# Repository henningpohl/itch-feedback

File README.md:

# Itch Feedback
This is a repository for content related to the [*ElectricItch: Skin Irritation as a Feedback Modality*](https://doi.org/10.1145/3242587.3242647) paper, published at [UIST 2018](https://uist.acm.org/uist2018/).

## Contents
At this point, this repository contains:
 - The paper itself
 - The schematics and board layout for [Autodesk EAGLE](https://www.autodesk.com/products/eagle/overview)
 - Firmware code for the [Adafruit Feather M0 Bluefruit LE](https://www.adafruit.com/product/2995), as a [Platform.IO](http://platformio.org/platformio-ide) project (likely works with other boards and IDEs)

## License
See the LICENSE file. Basically all our work is released under the MIT License --- do whatever you want with it. Note though that the firmware uses the [Timer5 library](https://github.com/michael71/Timer5), which is licensed under the GNU LGPL.

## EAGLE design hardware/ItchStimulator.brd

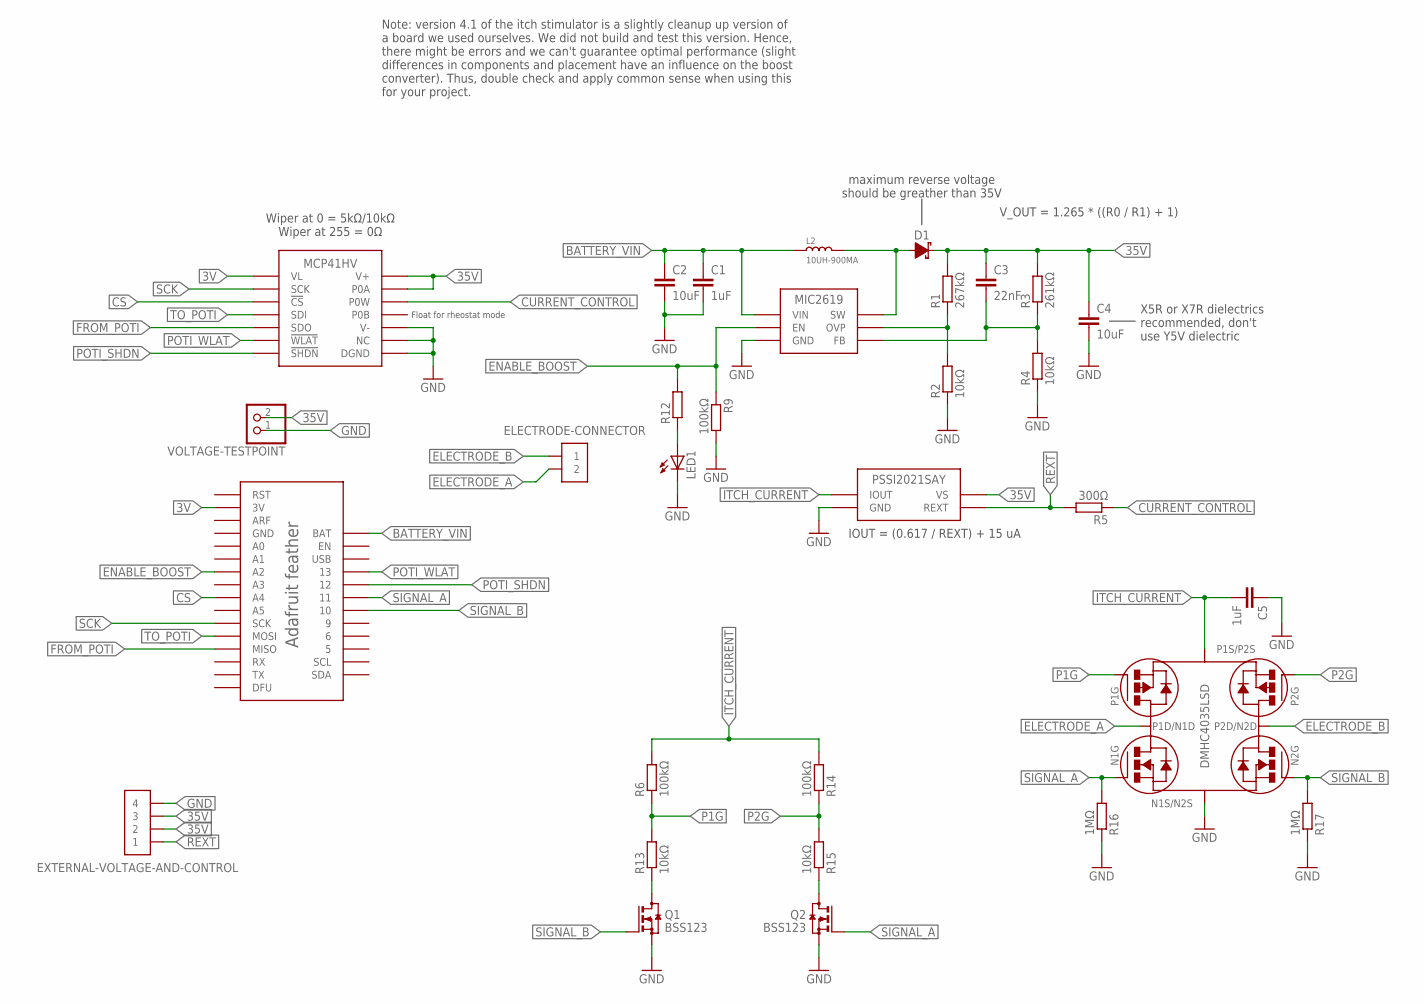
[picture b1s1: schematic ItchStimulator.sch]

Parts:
C1, C5: 1uF; C0805K
C2, C4: 10uF; C0805K
C3: 22nF; C0805K
D1: DIODE-SCHOTTKY; DO-214AA
ELECTRODE-CONNECTOR: 2-PIN_HEADER; SAMTEC-TSM-102-01-X-SH
EXTERNAL-VOLTAGE-AND-CONTROL: 4-PIN_HEADER; SAMTEC-TSM-104-01-X-SH
L2: 10UH-900MA; L1210
LED1: LEDSML0805; SML0805
MCP41HV: MCP41HV; TSSOP-14
MIC2619: MIC2619; TSOT-23-6
PSSI2021SAY: PSSI2021SAY; SOT-353
Q1, Q2: BSS123; SOT23
R1: 267kΩ; R0805
R2, R4, R13, R15: 10kΩ; R0805
R3: 261kΩ; R0805
R5: 300Ω; R0805
R6, R9, R14: 100kΩ; R0805
R12: R-EU_R0805; R0805
R16, R17: 1MΩ; R0805
U$1: ADAFRUIT_FEATHER_M0_BLUETOOTH
U$2: DMHC4035LSD; SOIC-8
VOLTAGE-TESTPOINT: PINHD-1X2; 1X02

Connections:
3V: MCP41HV.P$1 (VL), U$1.P$15 (3V)
35V: C3.1, C4.1, D1.CATHODE, EXTERNAL-VOLTAGE-AND-CONTROL.P$2 (2), EXTERNAL-VOLTAGE-AND-CONTROL.P$3 (3), MCP41HV.P$13 (P0A), MCP41HV.P$14 (V+), PSSI2021SAY.P$5 (VS), R1.2, R3.2, VOLTAGE-TESTPOINT.2
BATTERY_VIN: C1.1, C2.1, L2.1, MIC2619.P$6 (VIN), U$1.P$17 (BAT)
CS: MCP41HV.P$3 (!CS), U$1.P$8 (A4)
CURRENT_CONTROL: MCP41HV.P$12 (P0W), R5.1
ELECTRODE_A: ELECTRODE-CONNECTOR.P$2 (2), U$2.P$2 (P1D/N1D)
ELECTRODE_B: ELECTRODE-CONNECTOR.P$1 (1), U$2.P$6 (P2D/N2D)
ENABLE_BOOST: MIC2619.P$4 (EN), R9.1, R12.2, U$1.P$10 (A2)
FROM_POTI: MCP41HV.P$5 (SDO), U$1.P$4 (MISO)
GND: C1.2, C2.2, C4.2, C5.1, EXTERNAL-VOLTAGE-AND-CONTROL.P$4 (4), LED1.C, MCP41HV.P$8 (DGND), MCP41HV.P$9 (NC), MCP41HV.P$10 (V-), MIC2619.P$2 (GND), PSSI2021SAY.P$3 (GND), Q1.2 (S), Q2.2 (S), R2.1, R4.1, R9.2, R16.1, R17.1, U$1.P$13 (GND), U$2.P$3 (N1S/N2S), VOLTAGE-TESTPOINT.1
ITCH_CURRENT: C5.2, PSSI2021SAY.P$2 (IOUT), R6.2, R14.2, U$2.P$7 (P1S/P2S)
unnamed: D1.ANODE, L2.2, MIC2619.P$1 (SW)
unnamed: C3.2, MIC2619.P$3 (FB), R3.1, R4.2
unnamed: LED1.A, R12.1
unnamed: MIC2619.P$5 (OVP), R1.1, R2.2
unnamed: Q1.3 (D), R13.1
unnamed: Q2.3 (D), R15.1
P1G: R6.1, R13.2, U$2.P$8 (P1G)
P2G: R14.1, R15.2, U$2.P$5 (P2G)
POTI_SHDN: MCP41HV.P$7 (!SHDN), U$1.P$21 (12)
POTI_WLAT: MCP41HV.P$6 (!WLAT), U$1.P$20 (13)
REXT: EXTERNAL-VOLTAGE-AND-CONTROL.P$1 (1), PSSI2021SAY.P$4 (REXT), R5.2
SCK: MCP41HV.P$2 (SCK), U$1.P$6 (SCK)
SIGNAL_A: Q2.1 (G), R16.2, U$1.P$22 (11), U$2.P$1 (N1G)
SIGNAL_B: Q1.1 (G), R17.2, U$1.P$23 (10), U$2.P$4 (N2G)
TO_POTI: MCP41HV.P$4 (SDI), U$1.P$5 (MOSI)
USB: U$1.P$19 (USB)

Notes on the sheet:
X5R or X7R dielectrics recommended, don't use Y5V dielectric
maximum reverse voltage should be greather than 35V
V_OUT = 1.265 * ((R0 / R1) + 1)
IOUT = (0.617 / REXT) + 15 uA
Float for rheostat mode
Wiper at 0 = 5kΩ/10kΩ Wiper at 255 = 0Ω
Note: version 4.1 of the itch stimulator is a slightly cleanup up version of a board we used ourselves. We did not build and test this version. Hence, there might be errors and we can't guarantee optimal performance (slight differences in components and placement have an influence on the boost conv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

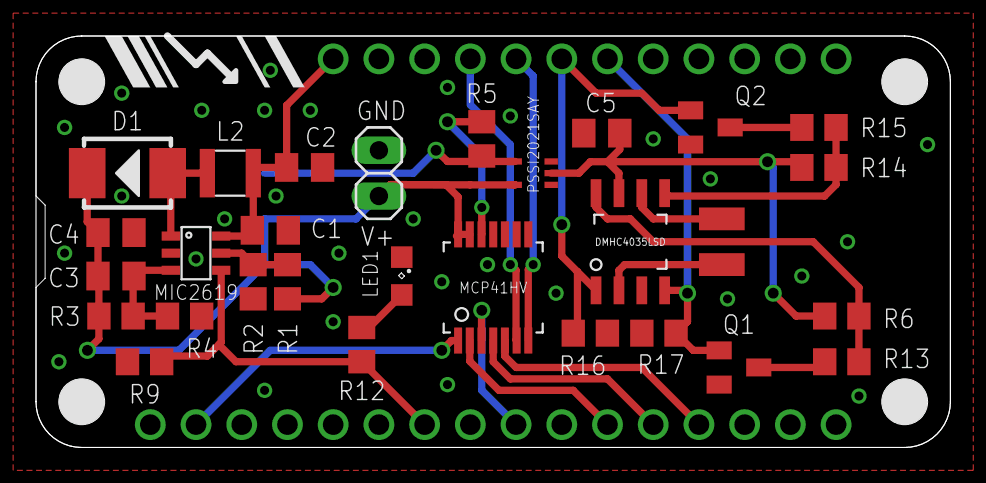
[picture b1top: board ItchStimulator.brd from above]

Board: 2 copper layers, 50.8 x 22.9 mm, 31 parts (1 on the bottom side), 26 nets.

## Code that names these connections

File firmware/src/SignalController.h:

#pragma once

#include "Timer5.h"
#include "MCP41HV.h"
#include "CommandParser.h"

const int SIGNAL_A = 11;
const int SIGNAL_B = 10;
const int BOOST_ENABLE = A2;

const int POTI_CS = A4;
const int POTI_WLAT = 13;
const int POTI_SHDN = 12;
MCP41HV poti(POTI_CS);

bool isTurnedOn = false;

#if INCLUDE_TESTS
  typedef void (* LoopFunction)();
  LoopFunction loopTestFunction = nullptr;
#endif


const uint16_t TIMER_TICKS = 32768;
const double MICROSECONDS_TO_TICKS = TIMER_TICKS / 1000000.0;
uint16_t signalToggle = 655; // 50Hz
uint16_t pulseToggle = 65; // 2ms pulse
uint16_t curTimerState = 0;

void Timer5_IRQ() {
  if(!isTurnedOn) {
    return;
  }

  if(curTimerState == 0) {
    digitalWrite(SIGNAL_A, HIGH);
  } else if(curTimerState == pulseToggle) {
    digitalWrite(SIGNAL_A, LOW);
  } else if(curTimerState == pulseToggle + 20) {
    digitalWrite(SIGNAL_B, HIGH);
  } else if(curTimerState == (2 * pulseToggle + 20)) {
    digitalWrite(SIGNAL_B, LOW);
  }
  
  curTimerState = (curTimerState + 1) % (signalToggle + 1);
}

void onParameterChange(SignalParameters & params) {
  poti.writeWiperValue(params.amplitude);
  signalToggle = TIMER_TICKS / params.frequency;
  pulseToggle = params.pulseWidth * MICROSECONDS_TO_TICKS; 
  curTimerState = 0;
}

void setupSignal() {
  pinMode(POTI_WLAT, OUTPUT);
  pinMode(POTI_SHDN, OUTPUT);
  pinMode(SIGNAL_A, OUTPUT);
  pinMode(SIGNAL_B, OUTPUT);
  pinMode(BOOST_ENABLE, OUTPUT);

  poti.setup();
  SPI.begin();

  MyTimer5.begin(1); // run at full 32768 Hz
  MyTimer5.attachInterrupt(Timer5_IRQ);

  digitalWrite(BOOST_ENABLE, LOW);
  digitalWrite(POTI_WLAT, LOW); // Don't delay wiper value updates
  digitalWrite(POTI_SHDN, LOW); // Shut down initially
  digitalWrite(SIGNAL_A, LOW);
  digitalWrite(SIGNAL_B, LOW);
}

void turnOnSignal() {
#if INCLUDE_TESTS
  loopTestFunction = nullptr;
#endif

  isTurnedOn = true;
  digitalWrite(BOOST_ENABLE, HIGH);
  digitalWrite(POTI_SHDN, HIGH);
  MyTimer5.begin(1); // run at full 32768 Hz
  MyTimer5.start();
}

void turnOffSignal() {
#if INCLUDE_TESTS
  loopTestFunction = nullptr;
#endif

  isTurnedOn = false;
  digitalWrite(BOOST_ENABLE, LOW);
  digitalWrite(POTI_SHDN, LOW);
  MyTimer5.end();
}

#if INCLUDE_TESTS
void constantTestSignal(uint8_t strength) {
  isTurnedOn = false;
  MyTimer5.end();
  digitalWrite(BOOST_ENABLE, HIGH);
  digitalWrite(POTI_SHDN, HIGH);
  poti.writeWiperValue(strength);
  digitalWrite(SIGNAL_A, LOW);
  digitalWrite(SIGNAL_B, HIGH);

}

uint8_t rampTestState;
void rampLoopFunction() {
  poti.writeWiperValue(rampTestState);
  rampTestState--;
  digitalWrite(SIGNAL_A, LOW);
  digitalWrite(SIGNAL_B, HIGH);
  delayMicroseconds(2000);
  digitalWrite(SIGNAL_A, LOW);
  digitalWrite(SIGNAL_B, LOW);
}

void rampTestSignal() {
  isTurnedOn = false;
  MyTimer5.end();
  digitalWrite(BOOST_ENABLE, HIGH);
  digitalWrite(POTI_SHDN, HIGH);
  digitalWrite(SIGNAL_A, LOW);
  digitalWrite(SIGNAL_B, LOW);
  rampTestState = 255;
  poti.writeWiperValue(rampTestState);
  loopTestFunction = rampLoopFunction;
}

void testSignalOutput() {
  digitalWrite(POTI_SHDN, HIGH);
  poti.writeWiperValue(234); // should be 1.5mA -> 15V over the 10k resistor
  isTurnedOn = true;
  MyTimer5.begin(1); // run at full 32768 Hz
  MyTimer5.start();
}

void testSignalOutput2() {
  digitalWrite(POTI_SHDN, HIGH);
  poti.writeWiperValue(220);
  digitalWrite(SIGNAL_B, HIGH);
  delay(2000);
  digitalWrite(SIGNAL_B, LOW);
  delay(2000);
  digitalWrite(SIGNAL_A, HIGH);
  delay(2000);
  digitalWrite(SIGNAL_A, LOW);
  delay(2000);
}

void selectTestMode(uint32_t testMode) {
  switch(testMode) {
    case 0:
      constantTestSignal(255);
      break;
    case 1:
      constantTestSignal(200);
      break;
    case 2:
      constantTestSignal(150);
      break;
    case 3:
      rampTestSignal();
      break;
  }
}
#endif

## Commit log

2018-10-09 Camera ready version of the paper
2018-10-09 Itch stimulator board v4.1
2018-10-09 Platform.IO project for itch stimulator firmware
